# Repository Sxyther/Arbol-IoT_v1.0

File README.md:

# Arbol IoT v1.0
Arbol IoT version 1.1 

---------------------------------------------------------------------------------------------------------------------
Software License: GPL v3

---------------------------------------------------------------------------------------------------------------------
Hardware License: CERN
Hardware released under an CERN Open Hardware Licence v1.2. See the LICENSE_HARDWARE file for more information.

---------------------------------------------------------------------------------------------------------------------
Documentation License: Creative Commons
Esta obra está bajo una Licencia Creative Commons Atribución-CompartirIgual 4.0 Internacional.

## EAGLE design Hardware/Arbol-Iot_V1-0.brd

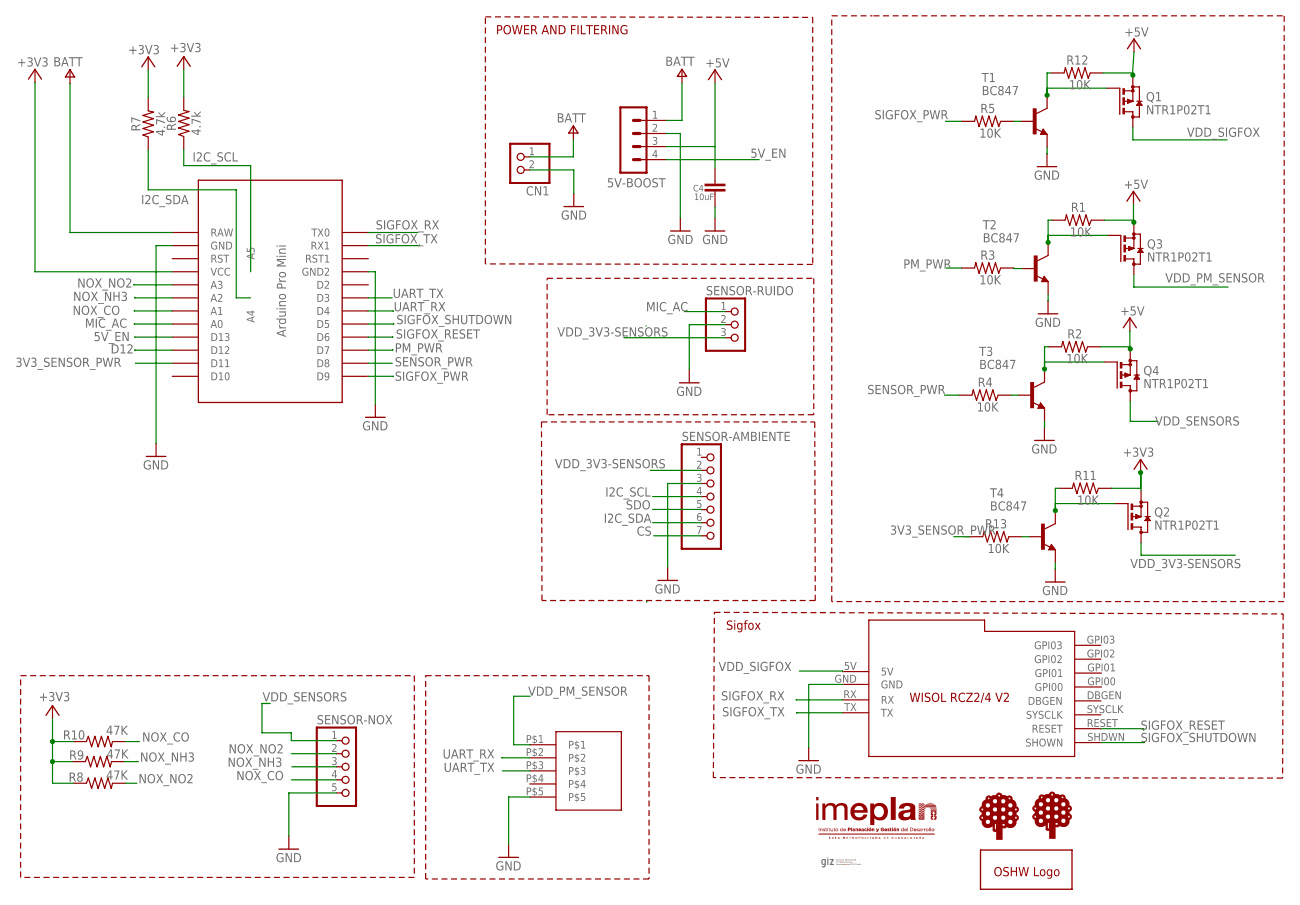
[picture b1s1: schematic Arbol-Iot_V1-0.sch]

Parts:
5V-BOOST: MA04-1
C4: 10uF; C1206
CN1: JST_2PIN-SMT-RA; JST-PH-2-SMT-RA
GOLD_ORB_SM1: OSHWLOGOLOGO5MM; OSHW_5MM
PM-SENSOR: S5B-ZR-3.4
Q1, Q2, Q3, Q4: NTR1P02T1; SOT23
R1, R2, R3, R4, R5, R11, R12, R13: 10K; 1206
R6, R7: 4.7k; 1206
R8, R9, R10: 47K; 1206
SENSOR-AMBIENTE: PINHD-1X7; 1X07
SENSOR-NOX: PINHD-1X5; 1X05
SENSOR-RUIDO: PINHD-1X3; 1X03
T1, T2, T3, T4: BC847; SOT23
U$1: GIZ-LOGO
U$2: WISOL-RCZ2/4V2; BREAKOUT-WISOL-SIGFOX
U$3, U$6: ARBOL-IOT-LETRAS
U$4: BAST
U$7: IMEPLAN-LOGO

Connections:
3V3_SENSOR_PWR: R13.2, U$4.D11
5V_EN: 5V-BOOST.4, U$4.D13
+3V3: Q2.2 (S), R6.2, R7.2, R8.1, R9.1, R10.1, R11.1, U$4.VCC
+5V: 5V-BOOST.3, C4.1, Q1.2 (S), Q3.2 (S), Q4.2 (S), R1.1, R2.1, R12.1
CS: SENSOR-AMBIENTE.7
D12: U$4.D12
GND: 5V-BOOST.2, C4.2, CN1.2 (1), PM-SENSOR.P$5, SENSOR-AMBIENTE.3, SENSOR-NOX.5, SENSOR-RUIDO.2, T1.2 (E), T2.2 (E), T3.2 (E), T4.2 (E), U$2.GND, U$4.GND, U$4.GND1 (GND2)
I2C_SCL: R6.1, SENSOR-AMBIENTE.4, U$4.A5
I2C_SDA: R7.1, SENSOR-AMBIENTE.6, U$4.A4
MIC_AC: SENSOR-RUIDO.1, U$4.A0
unnamed: R5.1, T1.1 (B)
unnamed: R3.1, T2.1 (B)
unnamed: R4.1, T3.1 (B)
unnamed: Q2.1 (G), R11.2, T4.3 (C)
unnamed: Q1.1 (G), R12.2, T1.3 (C)
unnamed: Q3.1 (G), R1.2, T2.3 (C)
unnamed: Q4.1 (G), R2.2, T3.3 (C)
unnamed: R13.1, T4.1 (B)
NOX_CO: R10.2, SENSOR-NOX.4, U$4.A1
NOX_NH3: R9.2, SENSOR-NOX.3, U$4.A2
NOX_NO2: R8.2, SENSOR-NOX.2, U$4.A3
PM_PWR: R3.2, U$4.D7
SDO: SENSOR-AMBIENTE.5
SENSOR_PWR: R4.2, U$4.D8
SIGFOX_PWR: R5.2, U$4.D9
SIGFOX_RESET: U$2.RESET, U$4.D6
SIGFOX_RX: U$2.RX, U$4.TX0
SIGFOX_SHUTDOWN: U$2.SHDWN (SHOWN), U$4.D5
SIGFOX_TX: U$2.TX, U$4.RX1
UART_RX: PM-SENSOR.P$2, U$4.D4
UART_TX: PM-SENSOR.P$3, U$4.D3
V+: 5V-BOOST.1, CN1.1 (2), U$4.RAW
VDD_3V3-SENSORS: Q2.3 (D), SENSOR-AMBIENTE.2, SENSOR-RUIDO.3
VDD_PM_SENSOR: PM-SENSOR.P$1, Q3.3 (D)
VDD_SENSORS: Q4.3 (D), SENSOR-NOX.1
VDD_SIGFOX: Q1.3 (D), U$2.5V

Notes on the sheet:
POWER AND FILTERING
Sigfox

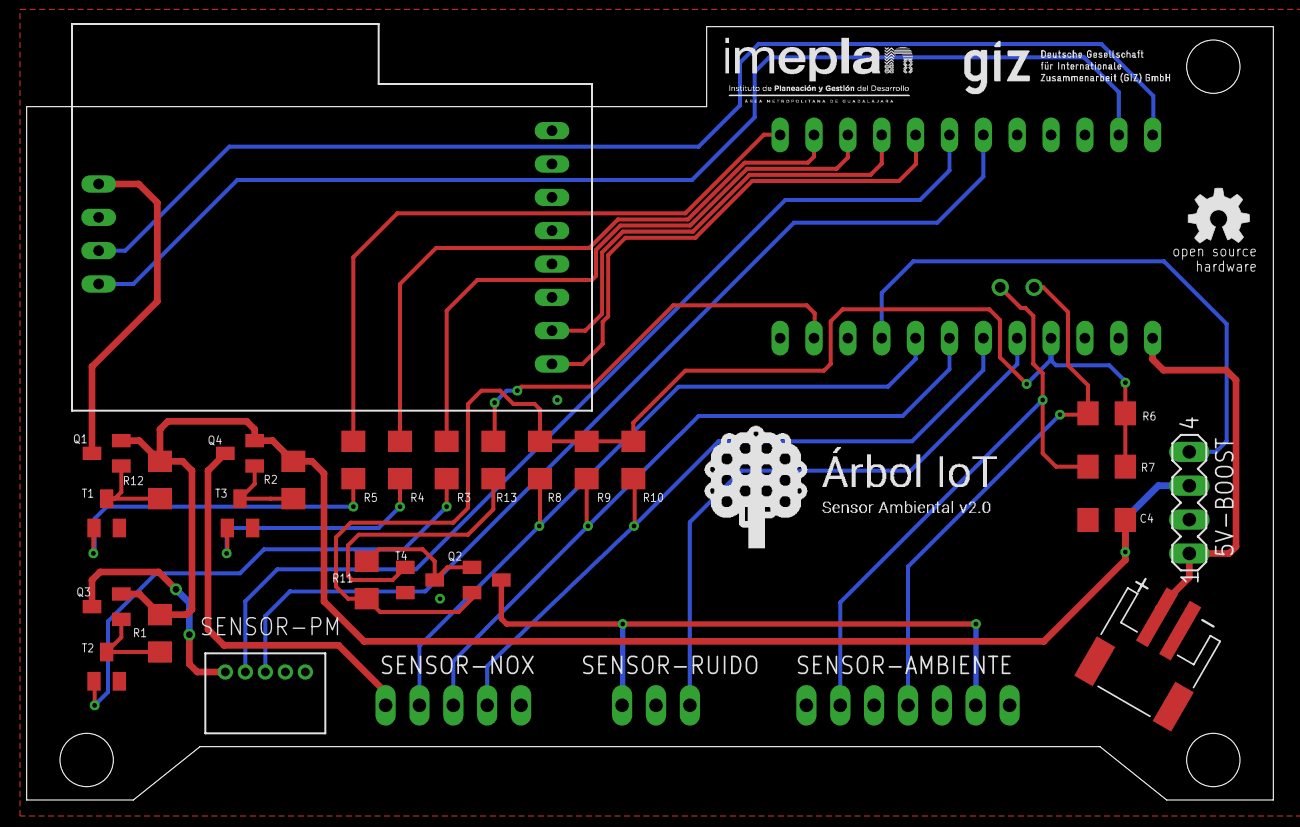
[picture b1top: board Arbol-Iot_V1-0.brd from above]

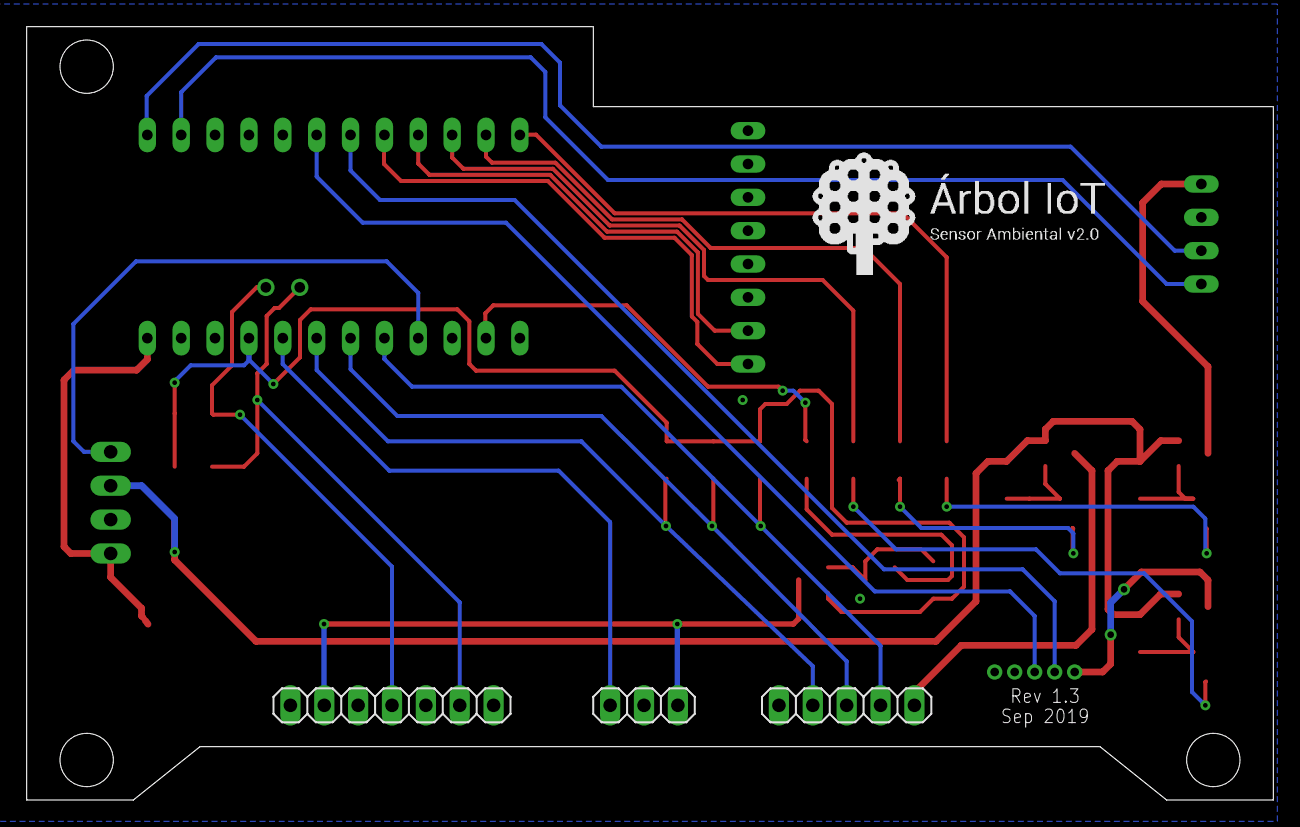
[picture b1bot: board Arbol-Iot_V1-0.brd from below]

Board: 2 copper layers, 93.5 x 58.0 mm, 35 parts (4 on the bottom side), 33 nets.

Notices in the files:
parts and their libraries:
SparkFun-Resistors: Licensing: Creative Commons ShareAlike 4.0 International - https://creativecommons.org/licenses/by-sa/4.0
